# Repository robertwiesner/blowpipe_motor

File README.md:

# Glassblowing adapter

This project is to build a blow pipe adapter to help with solo blowing. In contras to the external compressor to the blowpie using a hose. 
The goals include
* Identic PCB for blowpipe and wireless controller
* Easy configurable
* Using Wifi or Bluetooth as communication between the remote control and blow piep adapter
* Measuring the set and create air pressure
* Worktime at last 4 hours on one charge
* Reasonable cost effective

I'm using a Rasperry Pi Pico W running Micropython.

The repository contains
* Schematics for the PCB
* FreeCAD 0.21 models with easy adjustments for the adapter and remote control

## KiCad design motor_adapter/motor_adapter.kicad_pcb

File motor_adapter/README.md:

The PCB layout files using KICAD

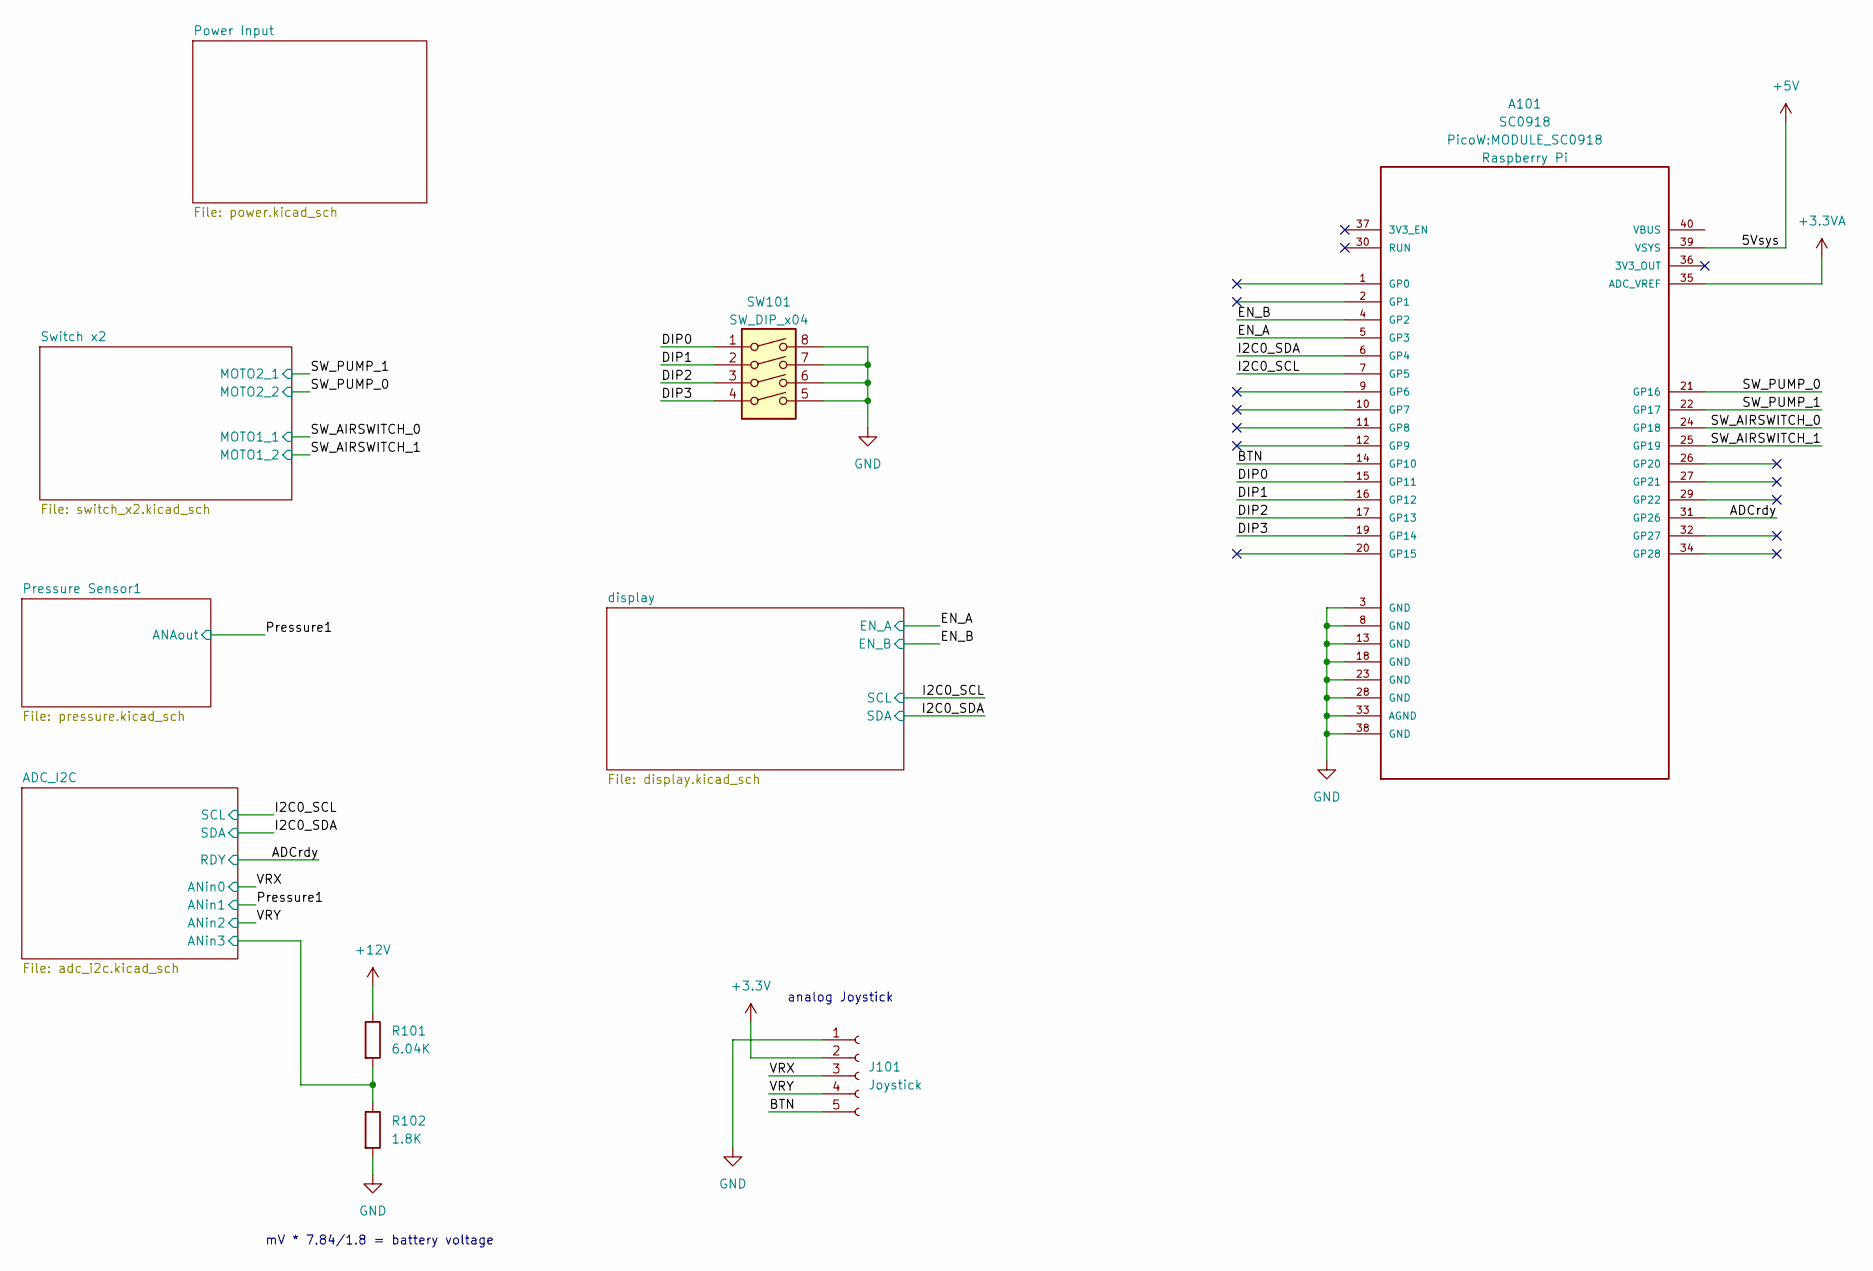
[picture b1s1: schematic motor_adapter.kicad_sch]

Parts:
A101: SC0918; MODULE_SC0918; PARTREV 1.6
J101: Joystick; PinHeader_1x05_P2.54mm_Vertical
R101: 6.04K; R_0402_1005Metric; Part 0402WGF2001TCE; LCSC C852895
R102: 1.8K; R_0402_1005Metric; Part 0402WGF2001TCE; LCSC C852621
SW101: SW_DIP_x04; SW_DIP_SPSTx04_Slide_Copal_CHS-04B_W7.62mm_P1.27mm; LCSC C845385

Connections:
+3.3V: J101.2; also elsewhere on the board
+3.3VA: A101.35 (ADC_VREF); also elsewhere on the board
/ADC_I2C/ANin3: R101.2, R102.1; also elsewhere on the board
/ADCrdy: A101.31 (GP26); also elsewhere on the board
/BTN: A101.14 (GP10), J101.5
/DIP0: A101.15 (GP11), SW101.1
/DIP1: A101.16 (GP12), SW101.2
/DIP2: A101.17 (GP13), SW101.3
/DIP3: A101.19 (GP14), SW101.4
/EN_A: A101.5 (GP3)
/EN_B: A101.4 (GP2)
/I2C0_SCL: A101.7 (GP5); also elsewhere on the board
/I2C0_SDA: A101.6 (GP4); also elsewhere on the board
/SW_AIRSWITCH_0: A101.24 (GP18); also elsewhere on the board
/SW_AIRSWITCH_1: A101.25 (GP19); also elsewhere on the board
/SW_PUMP_0: A101.21 (GP16); also elsewhere on the board
/SW_PUMP_1: A101.22 (GP17); also elsewhere on the board
/VRX: J101.3; also elsewhere on the board
/VRY: J101.4; also elsewhere on the board
GND: A101.3 (GND), A101.8 (GND), A101.13 (GND), A101.18 (GND), A101.23 (GND), A101.28 (GND), A101.33 (AGND), A101.38 (GND), J101.1, R102.2, SW101.5, SW101.6, SW101.7, SW101.8; also elsewhere on the board

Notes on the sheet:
mV * 7.84/1.8 = battery voltage
analog Joystick

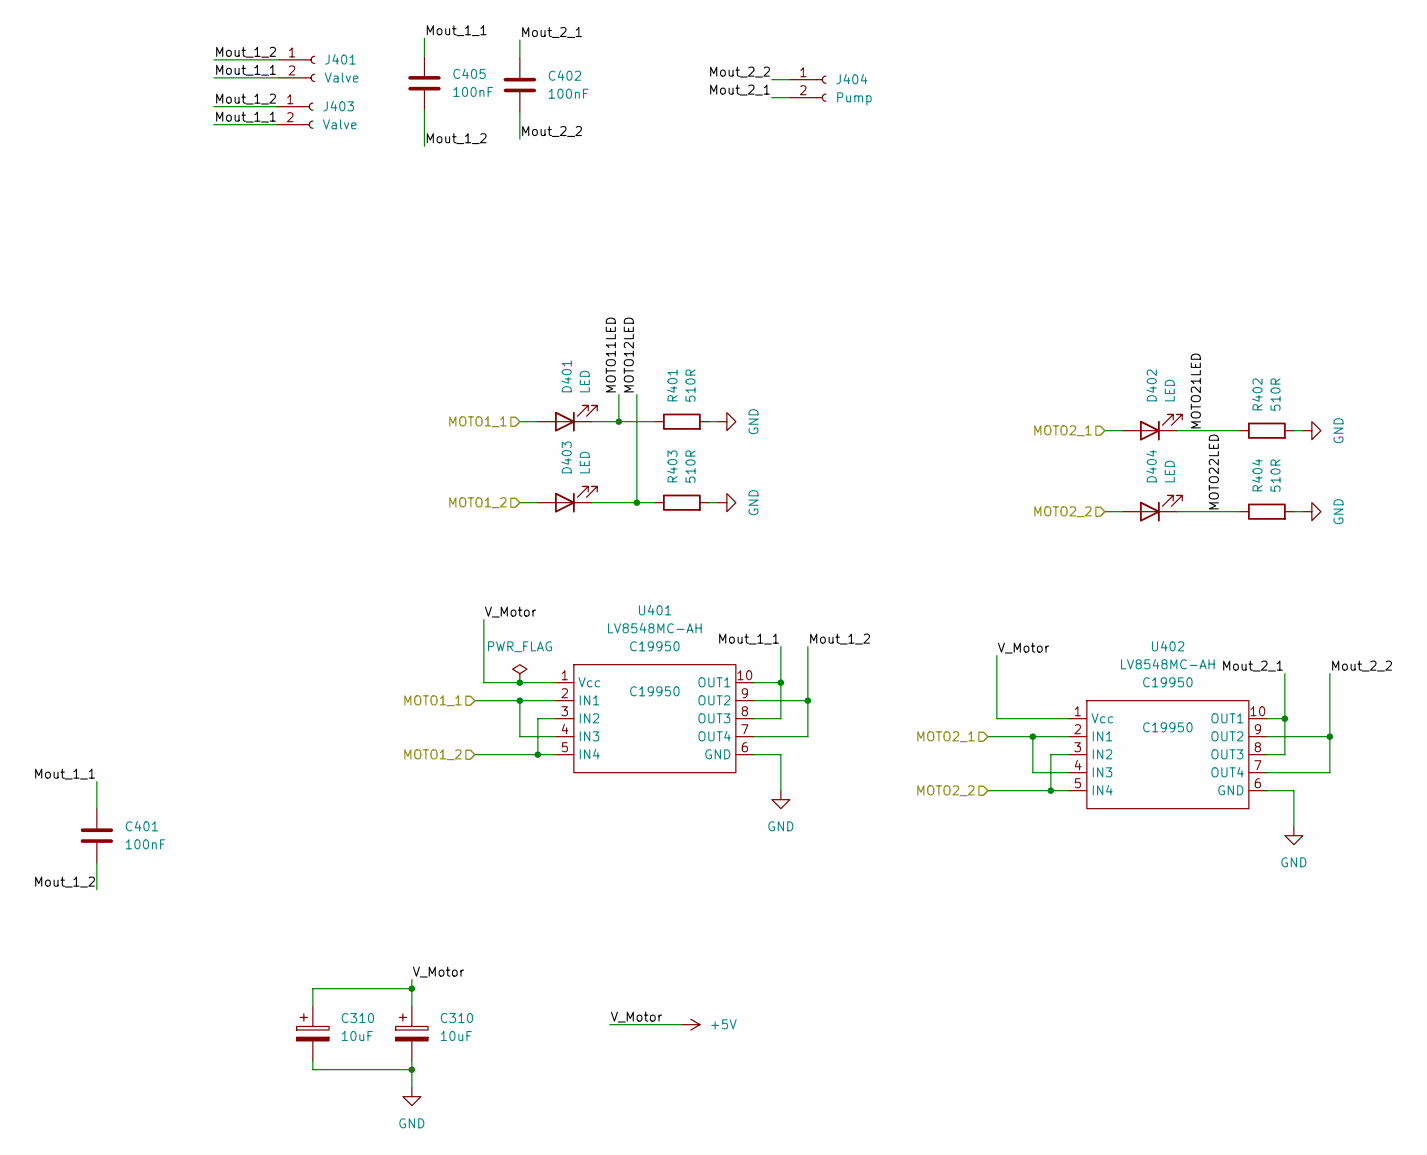
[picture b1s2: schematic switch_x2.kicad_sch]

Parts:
C310: 10uF; CP_EIA-3216-18_Kemet-A; LCSC C128254
C401, C402, C405: 100nF; C_0402_1005Metric; Part CL05B104KO5NNNC; LCSC C1525
D401, D402, D403, D404: LED; LED_0603_1608Metric; LCSC C72043
J401, J403: Valve; JST_XH_S2B-XH-A-1_1x02_P2.50mm_Horizontal
J404: Pump; JST_PH_S2B-PH-SM4-TB_1x02-1MP_P2.00mm_Horizontal
R401, R402, R403, R404: 510R; R_0402_1005Metric; LCSC C25123
U401, U402: LV8548MC-AH; SOIC-10-1mm; LCSC C19950

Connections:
/SW_AIRSWITCH_0: D401.2 (A), U401.2 (IN1), U401.4 (IN3); also elsewhere on the board
/SW_AIRSWITCH_1: D403.2 (A), U401.3 (IN2), U401.5 (IN4); also elsewhere on the board
/SW_PUMP_0: D404.2 (A), U402.3 (IN2), U402.5 (IN4); also elsewhere on the board
/SW_PUMP_1: D402.2 (A), U402.2 (IN1), U402.4 (IN3); also elsewhere on the board
/Switch x2/MOTO11LED: D401.1 (K), R401.1
/Switch x2/MOTO12LED: D403.1 (K), R403.1
/Switch x2/MOTO21LED: D402.1 (K), R402.1
/Switch x2/MOTO22LED: D404.1 (K), R404.1
/Switch x2/Mout_1_1: C401.1, C405.1, J401.2, J403.2, U401.8 (OUT3), U401.10 (OUT1)
/Switch x2/Mout_1_2: C401.2, C405.2, J401.1, J403.1, U401.7 (OUT4), U401.9 (OUT2)
/Switch x2/Mout_2_1: C402.1, J404.2, U402.8 (OUT3), U402.10 (OUT1)
/Switch x2/Mout_2_2: C402.2, J404.1, U402.7 (OUT4), U402.9 (OUT2)
GND: C310.2, R401.2, R402.2, R403.2, R404.2, U401.6 (GND), U402.6 (GND); also elsewhere on the board

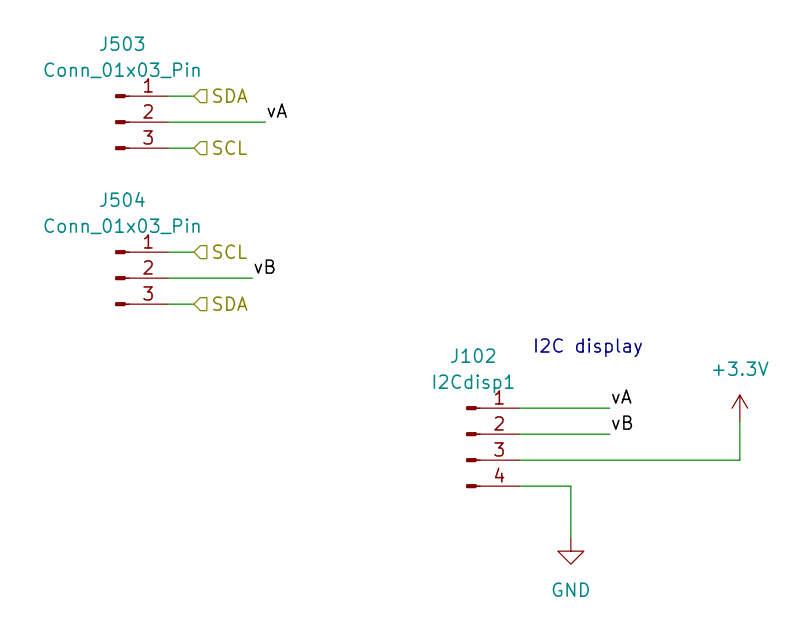
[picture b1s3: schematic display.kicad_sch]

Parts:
J102: I2Cdisp1; PinSocket_1x04_P2.54mm_Vertical
J503, J504: Conn_01x03_Pin; PinHeader_1x03_P2.54mm_Vertical

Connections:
/I2C0_SCL: J503.3, J504.1; also elsewhere on the board
/I2C0_SDA: J503.1, J504.3; also elsewhere on the board
/display/vA: J503.2; also elsewhere on the board
/display/vB: J504.2; also elsewhere on the board

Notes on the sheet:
I2C display

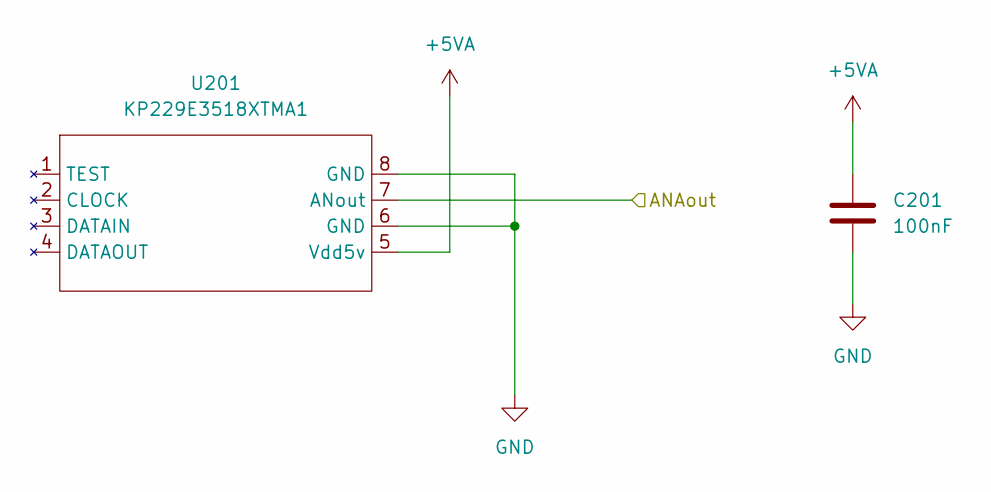
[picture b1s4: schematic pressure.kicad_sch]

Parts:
C201: 100nF; C_0402_1005Metric; Part CL05B104KO5NNNC; LCSC C1525
U201: KP229E3518XTMA1; PG-DSOF-8-16

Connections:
+5VA: C201.1, U201.5 (Vdd5v); also elsewhere on the board
/Pressure1: U201.7 (ANout); also elsewhere on the board
GND: C201.2, U201.6 (GND), U201.8 (GND); also elsewhere on the board

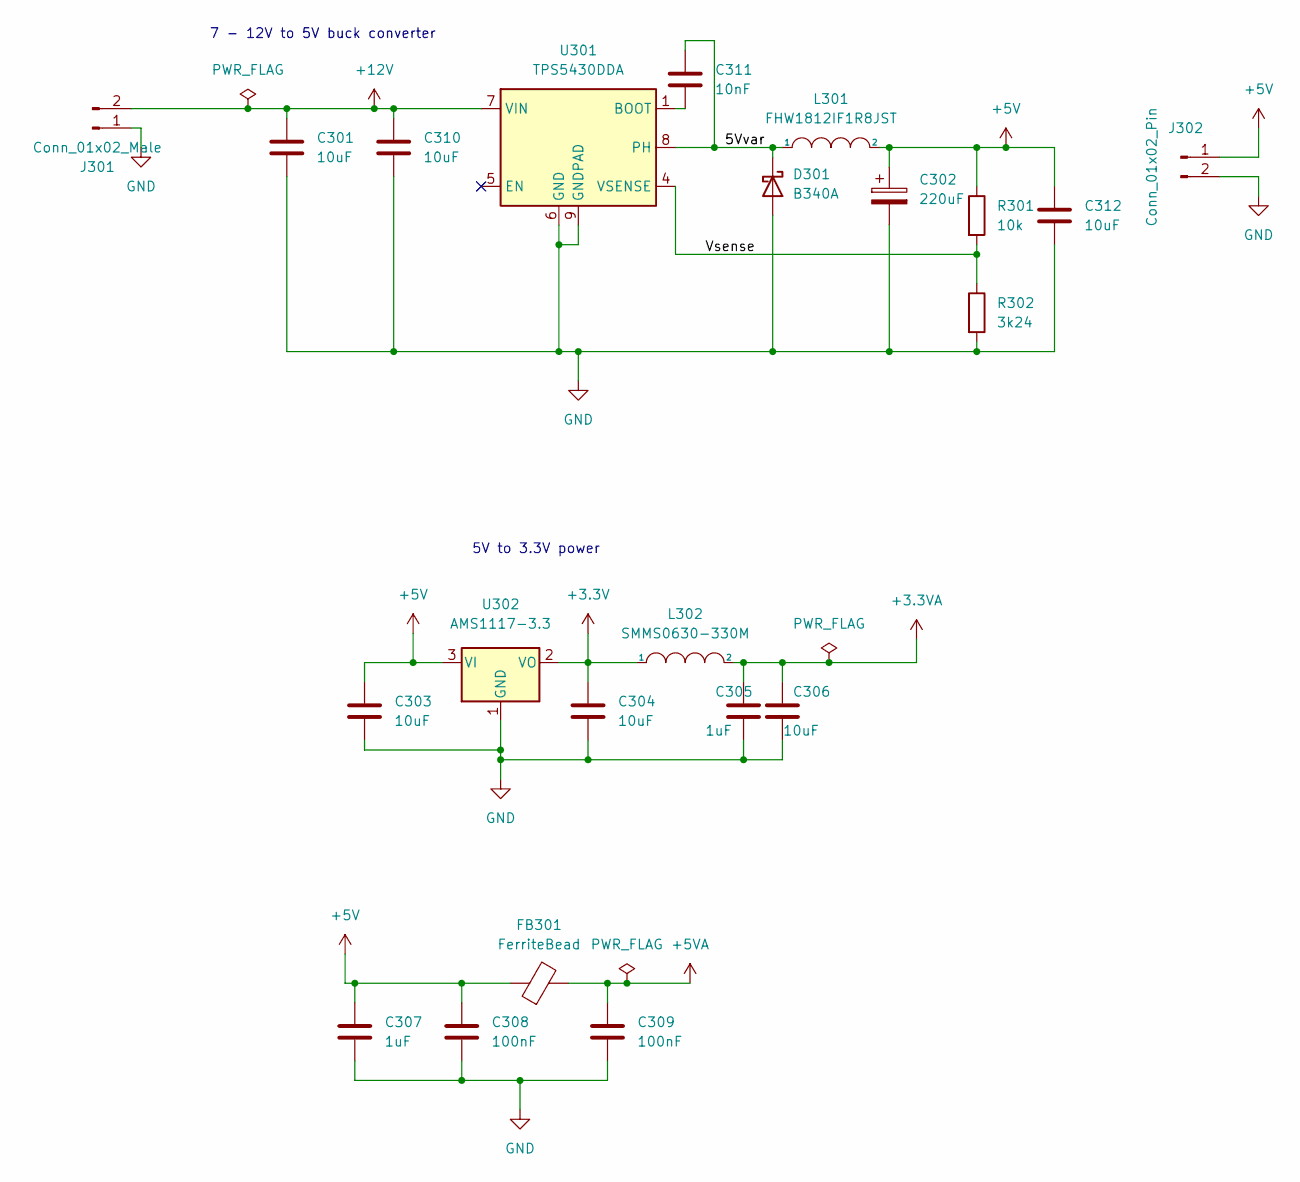
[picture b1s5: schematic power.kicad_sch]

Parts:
C301, C310, C312: 10uF; C_1206_3216Metric; LCSC C128855
C302: 220uF; CP_EIA-7343-31_Kemet-D; LCSC C8024
C303, C304, C306: 10uF; C_0603_1608Metric; LCSC C18800
C305: 1uF; C_0603_1608Metric; LCSC C92848
C307: 1uF; C_0402_1005Metric; LCSC C106254
C308, C309: 100nF; C_0402_1005Metric; LCSC C110251
C311: 10nF; C_0402_1005Metric; LCSC C2840480
D301: B340A; D_SMA; LCSC C3018525
FB301: FerriteBead; L_0603_1608Metric; LCSC C62708
J301: Conn_01x02_Male; AMASS_XT30U-F_1x02_P5.0mm_Vertical
J302: Conn_01x02_Pin; PinHeader_1x02_P2.54mm_Vertical
L301: FHW1812IF1R8JST; L_1812_4532Metric; LCSC C394113
L302: SMMS0630-330M; L_Bourns_SRP7028A_7.3x6.6mm; LCSC C149577
R301: 10k; R_0402_1005Metric; LCSC C60490
R302: 3k24; R_0402_1005Metric; LCSC C327346
U301: TPS5430DDA; TI_SO-PowerPAD-8_ThermalVias; LCSC C9864
U302: AMS1117-3.3; SOT-223; LCSC C347222

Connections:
+3.3V: C304.1, L302.1, U302.2 (VO); also elsewhere on the board
+3.3VA: C305.1, C306.1, L302.2; also elsewhere on the board
+5VA: C309.1, FB301.2; also elsewhere on the board
/Power Input/5Vvar: C311.2, D301.1 (K), L301.1, U301.8 (PH)
/Power Input/Vsense: R301.2, R302.1, U301.4 (VSENSE)
GND: C301.2, C302.2, C303.2, C304.2, C305.2, C306.2, C307.2, C308.2, C309.2, C310.2, C312.2, D301.2 (A), J301.1, J302.2, R302.2, U301.6 (GND), U301.9 (GNDPAD), U302.1 (GND); also elsewhere on the board
unnamed: C311.1, U301.1 (BOOT)

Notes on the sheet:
7 - 12V to 5V buck converter
5V to 3.3V power

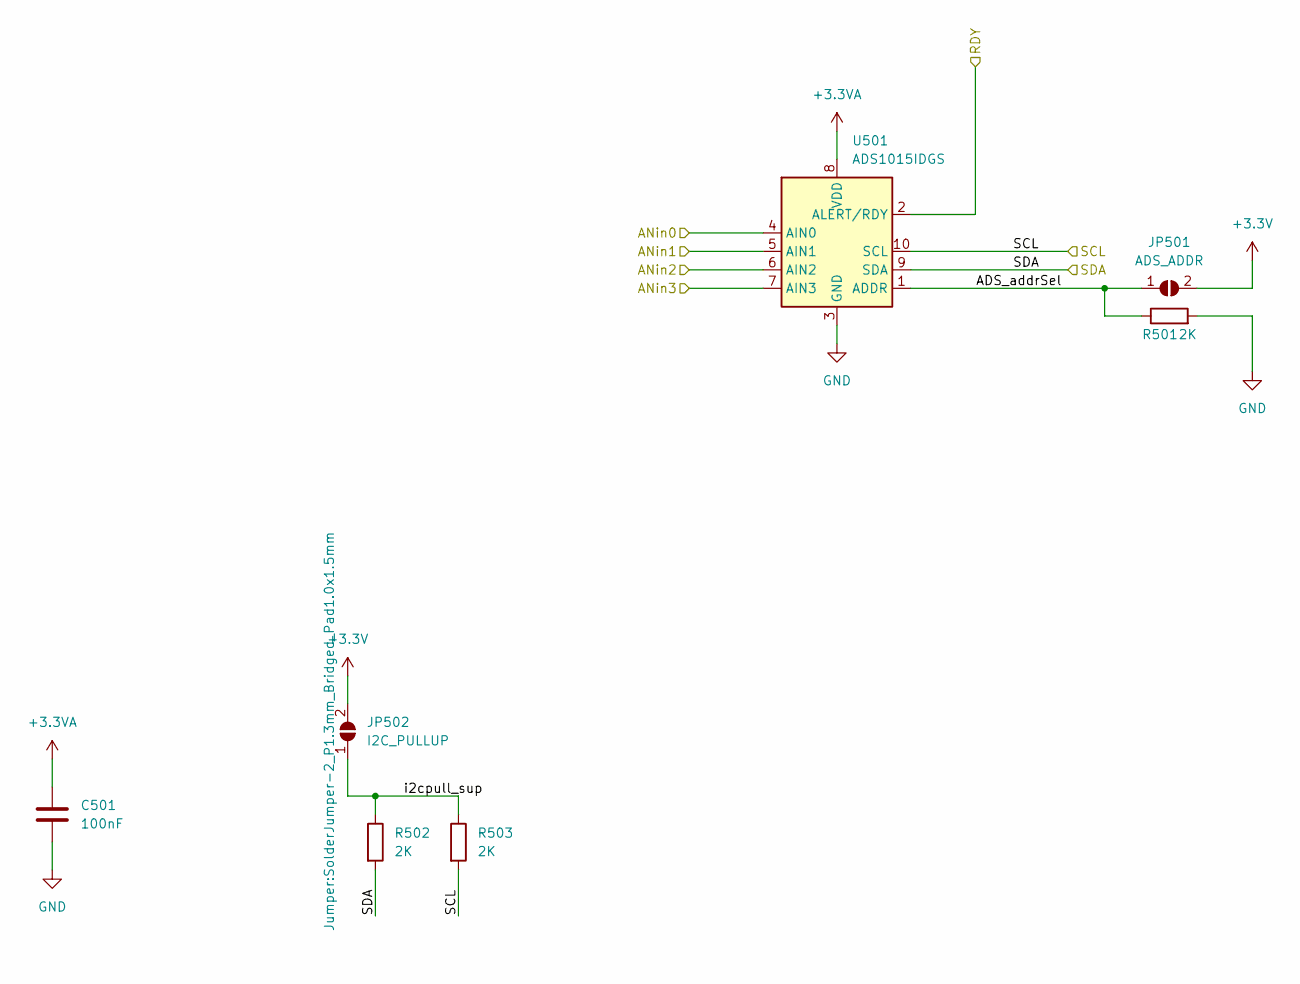
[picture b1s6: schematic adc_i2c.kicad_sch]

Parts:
C501: 100nF; C_0402_1005Metric; Part CL05B104KO5NNNC; LCSC C1525
JP501: ADS_ADDR; SolderJumper-2_P1.3mm_Open_RoundedPad1.0x1.5mm
JP502: I2C_PULLUP; SolderJumper-2_P1.3mm_Bridged_Pad1.0x1.5mm
R501, R502, R503: 2K; R_0402_1005Metric; Part 0402WGF2001TCE; LCSC C4109
U501: ADS1015IDGS; TSSOP-10_3x3mm_P0.5mm; LCSC C193969

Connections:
+3.3V: JP501.2 (B), JP502.2 (B); also elsewhere on the board
+3.3VA: C501.1, U501.8 (VDD); also elsewhere on the board
/ADC_I2C/ADS_addrSel: JP501.1 (A), R501.1, U501.1 (ADDR)
/ADC_I2C/ANin3: U501.7 (AIN3); also elsewhere on the board
/ADC_I2C/i2cpull_sup: JP502.1 (A), R502.1, R503.1
/ADCrdy: U501.2 (ALERT/RDY); also elsewhere on the board
/I2C0_SCL: R503.2, U501.10 (SCL); also elsewhere on the board
/I2C0_SDA: R502.2, U501.9 (SDA); also elsewhere on the board
/Pressure1: U501.5 (AIN1); also elsewhere on the board
/VRX: U501.4 (AIN0); also elsewhere on the board
/VRY: U501.6 (AIN2); also elsewhere on the board
GND: C501.2, R501.2, U501.3 (GND); also elsewhere on the board

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
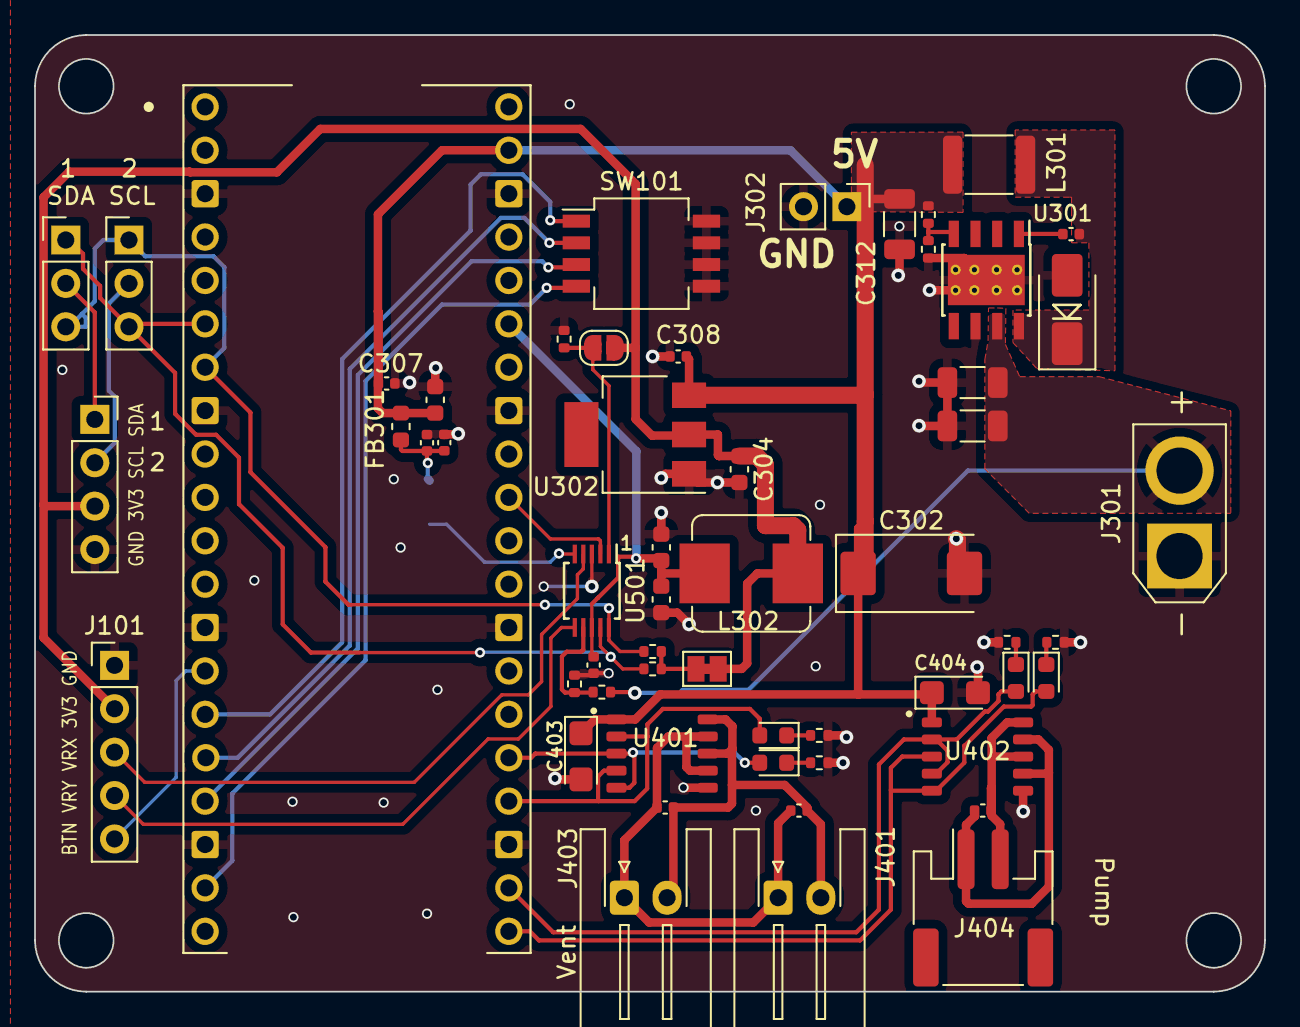
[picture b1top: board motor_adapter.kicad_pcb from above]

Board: 2 copper layers, 72.0 x 56.0 mm, 57 parts (1 on the bottom side), 37 nets.

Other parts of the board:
C403, C404: 10uF; CP_EIA-3216-18_Kemet-A
J501: I2Cdisp1; PinSocket_1x04_P2.54mm_Vertical

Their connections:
+3.3V: J501.3; also elsewhere on the board
/display/vA: J501.1; also elsewhere on the board
/display/vB: J501.2; also elsewhere on the board
GND: C403.2, C404.2, J501.4; also elsewhere on the board

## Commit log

2023-08-15 Create .gitignore
    inital list
2023-08-15 Add first version to Gitrepository
2023-08-15 add 3D models
2023-08-15 remove version extension
